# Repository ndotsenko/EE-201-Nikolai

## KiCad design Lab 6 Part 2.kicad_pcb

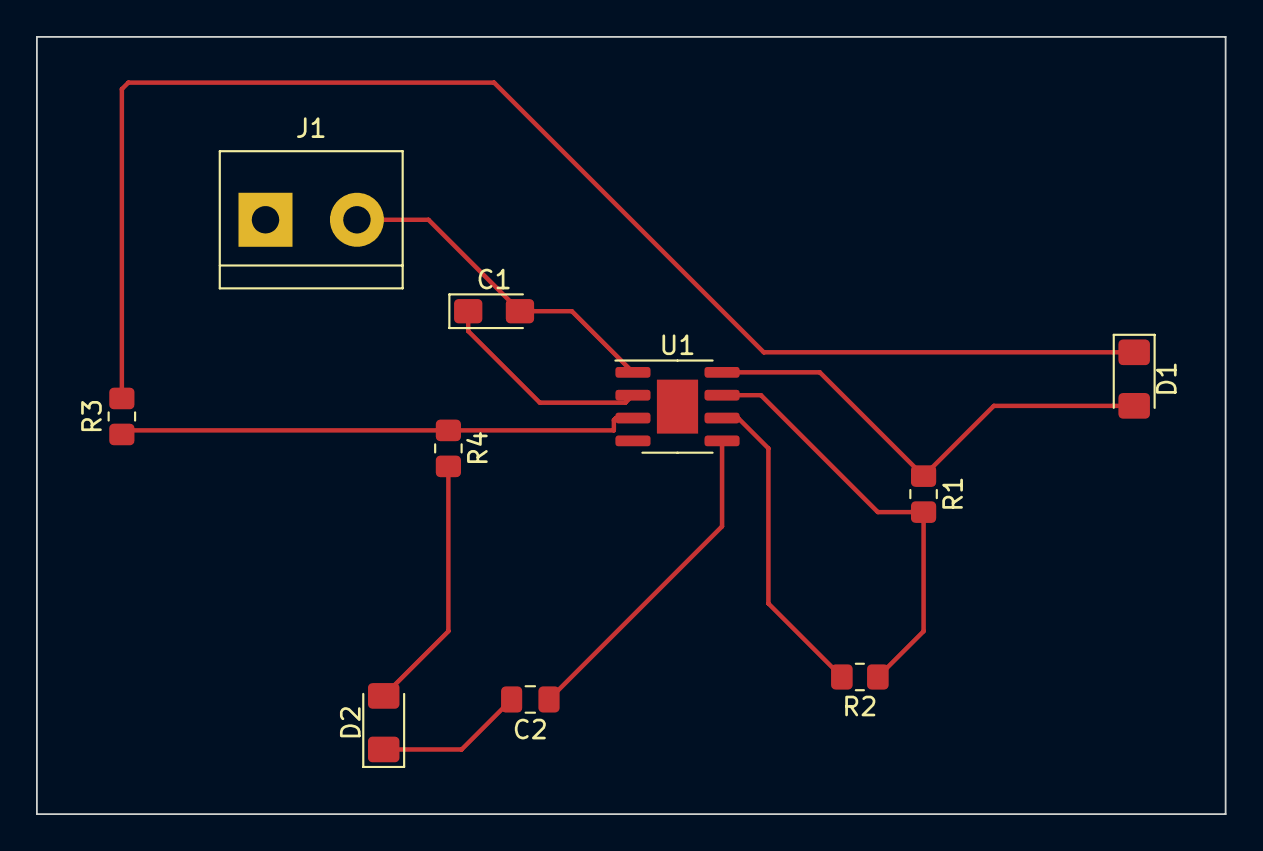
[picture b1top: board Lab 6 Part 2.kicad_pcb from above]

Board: 2 copper layers, 66.0 x 43.2 mm, 10 parts (0 on the bottom side), 8 nets.

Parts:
C1: 10uF; CP_EIA-3216-18_Kemet-A_Pad1.58x1.35mm_HandSolder
C2: 0.01uF; C_0805_2012Metric_Pad1.18x1.45mm_HandSolder
D1, D2: LED; LED_1206_3216Metric_Pad1.42x1.75mm_HandSolder
J1: Conn_01x02_Male; TerminalBlock_bornier-2_P5.08mm
R1, R3, R4: 1k; R_0805_2012Metric_Pad1.20x1.40mm_HandSolder
R2: 10k; R_0805_2012Metric_Pad1.20x1.40mm_HandSolder
U1: NE555D; SOIC-8-1EP_3.9x4.9mm_P1.27mm_EP2.29x3mm

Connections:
/pin_2: C1.1, R2.2, U1.2 (TR), U1.6 (THR)
/pin_3: R3.1, R4.1, U1.3 (Q)
/pin_7: R1.2, R2.1, U1.7 (DIS)
Earth: C1.2, C2.2, D2.1 (K), J1.2, U1.1 (GND)
unnamed: C2.1, U1.5 (CV)
unnamed: D1.1 (K), R3.2
unnamed: D1.2 (A), R1.1, U1.4 (R), U1.8 (VCC)
unnamed: D2.2 (A), R4.2

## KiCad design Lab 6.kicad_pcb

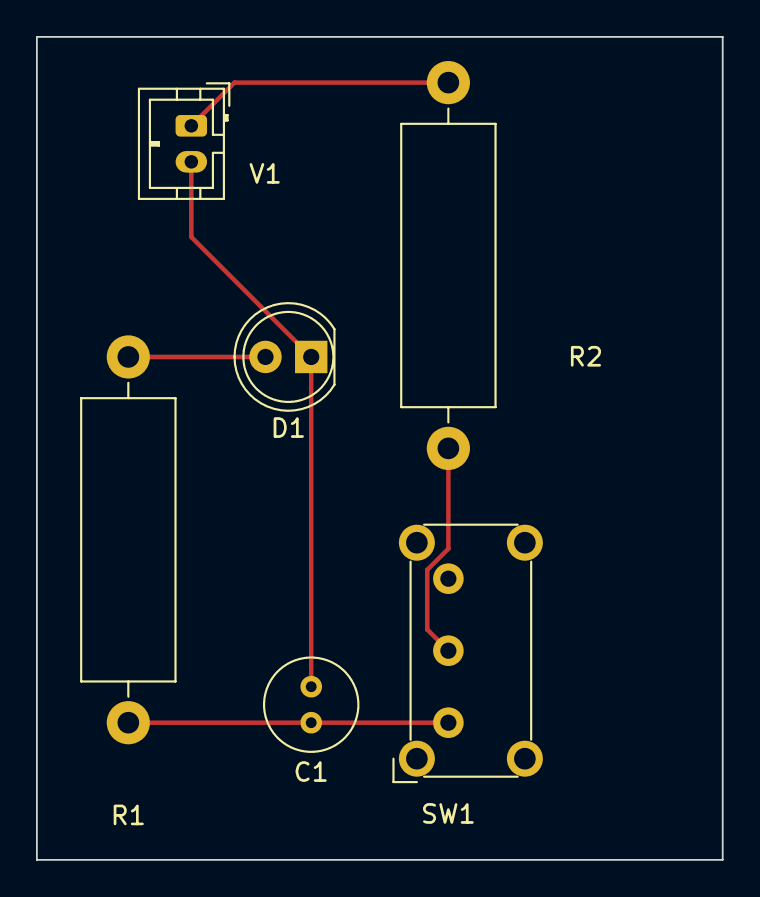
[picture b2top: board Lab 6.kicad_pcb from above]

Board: 2 copper layers, 38.1 x 45.7 mm, 6 parts (0 on the bottom side), 5 nets.

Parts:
C1: 4.7 μF; C_Radial_D5.0mm_H5.0mm_P2.00mm
D1: LED; LED_D5.0mm
R1: 20 kΩ; R_Axial_DIN0516_L15.5mm_D5.0mm_P20.32mm_Horizontal
R2: 2.2 kΩ; R_Axial_DIN0516_L15.5mm_D5.0mm_P20.32mm_Horizontal
SW1: SW_SPDT; SW_E-Switch_EG1224_SPDT_Angled
V1: 9 V; JST_PH_B2B-PH-K_1x02_P2.00mm_Vertical

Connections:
unnamed: C1.2, D1.1 (K), V1.2
unnamed: D1.2 (A), R1.2
unnamed: R2.1, SW1.2 (B)
unnamed: R2.2, V1.1
unnamed: C1.1, R1.1, SW1.1 (A)

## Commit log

2023-01-13 Added about me directory
